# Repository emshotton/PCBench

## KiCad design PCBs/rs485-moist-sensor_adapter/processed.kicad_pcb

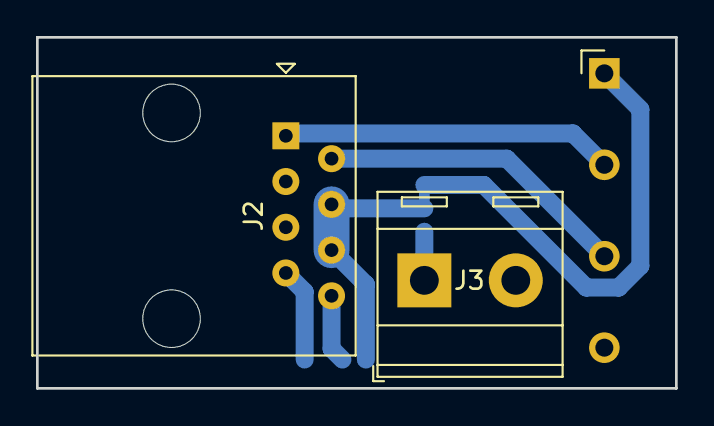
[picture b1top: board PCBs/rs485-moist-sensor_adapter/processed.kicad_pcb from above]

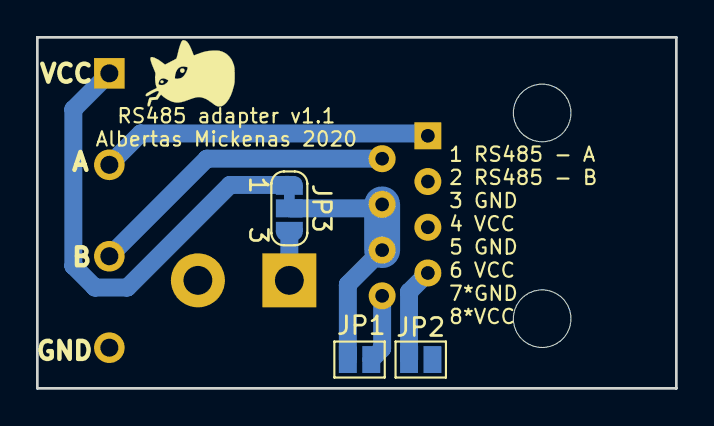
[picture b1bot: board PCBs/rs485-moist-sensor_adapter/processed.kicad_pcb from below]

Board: 2 copper layers, 35.5 x 19.5 mm, 6 parts (3 on the bottom side), 8 nets.

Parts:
J1: Conn_01x04_Male; Pin_Header_Angled_1x04_Pitch2.54mm
J2: RJ45; RJ45_Amphenol_54602-x08_Horizontal
J3: Conn_01x02_Male; TerminalBlock_RND_205-00287_Pitch5.08mm
JP1, JP2: Jumper_2_Open; SolderJumper-2_P1.3mm_Open_Pad1.0x1.5mm
JP3: Jumper_3_Bridged12; SolderJumper-3_P1.3mm_Bridged12_RoundedPad1.0x1.5mm_NumberL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

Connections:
/A: J1.2, J2.1
/A/GND: J2.7, JP2.1
/B: J1.3, J2.2
/B/VCC: J2.8, JP1.1
GND: J1.4, J2.3, J2.5, J3.2, JP2.2
unnamed: J1.1, JP3.1
unnamed: J3.1, JP3.3
VCC: J2.4, J2.6, JP1.2, JP3.2

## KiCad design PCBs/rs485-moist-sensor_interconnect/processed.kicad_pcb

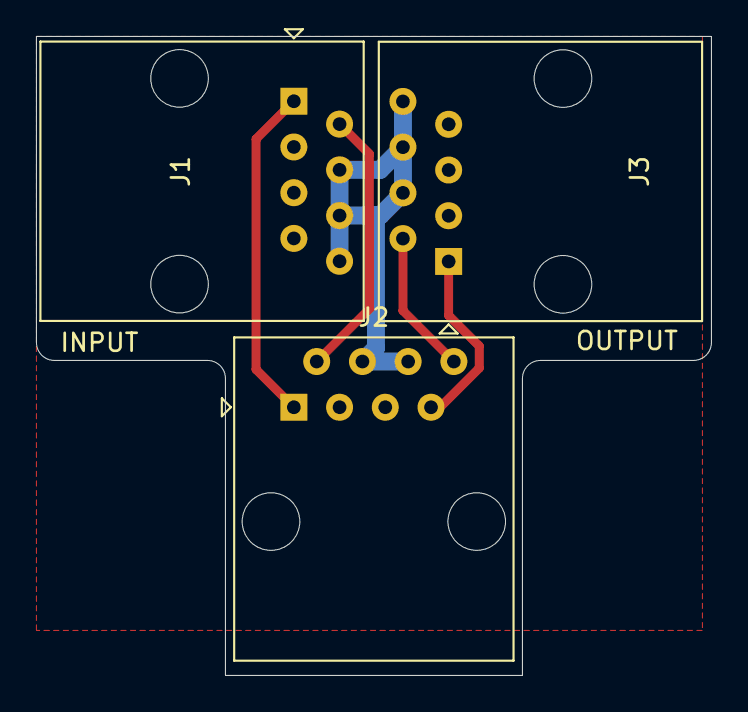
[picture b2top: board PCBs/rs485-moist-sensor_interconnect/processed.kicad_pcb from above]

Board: 2 copper layers, 37.5 x 35.5 mm, 4 parts (1 on the bottom side), 6 nets.

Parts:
C1: C; C_0603_1608Metric_Pad1.05x0.95mm_HandSolder
J1, J2, J3: RJ45; RJ45_Amphenol_54602-x08_Horizontal

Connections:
GND: C1.2, J1.3, J1.5, J1.7, J2.3, J2.5, J3.3, J3.5, J3.7
unnamed: J1.1, J2.1
unnamed: J1.2, J2.2
unnamed: J2.7, J3.1
unnamed: J2.8, J3.2
VCC: C1.1, J1.4, J1.6, J1.8, J2.4, J2.6, J3.4, J3.6, J3.8

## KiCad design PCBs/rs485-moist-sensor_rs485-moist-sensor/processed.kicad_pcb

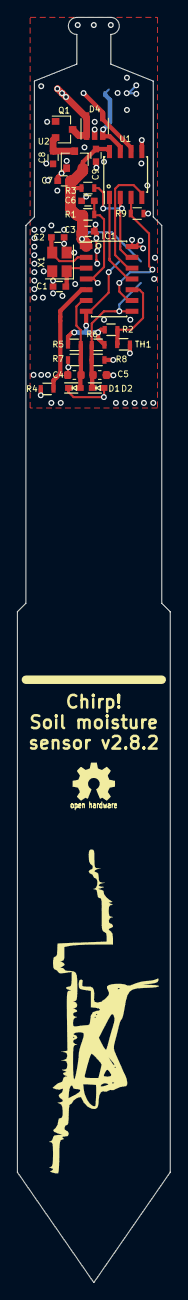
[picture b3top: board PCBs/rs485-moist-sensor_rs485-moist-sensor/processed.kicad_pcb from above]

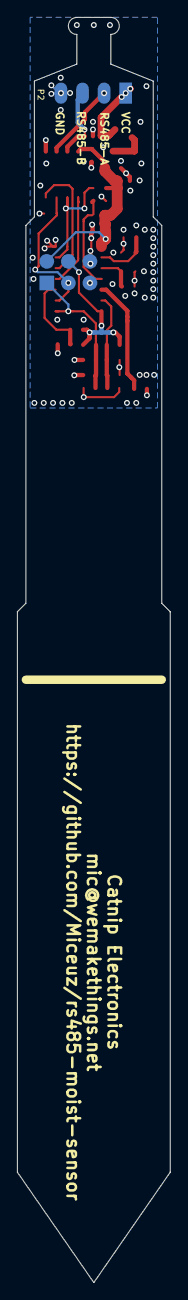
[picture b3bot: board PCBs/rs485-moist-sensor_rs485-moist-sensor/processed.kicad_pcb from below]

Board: 4 copper layers, 18.0 x 149.0 mm, 29 parts (2 on the bottom side), 19 nets.

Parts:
C1, C2: 13p; C_0603
C3, C6, C7, C8, C9: 1u; C_0603
C4, C5: 1n; C_0603_1608Metric
D1, D2: RB751S40; SOD-523
D4: NUP4004M5T1G; SOT-23-5
IC1: ATTINY441-SSU; SOIC-14_3.9x8.7mm_Pitch1.27mm
P1: CONN_02X03; Pin_Header_Straight_2x03
P2: CONN_01X04; Pin_Header_Straight_1x04_Pitch2.54mm
Q1: Q_PMOS_GSD; SOT-23
R1, R3, R9: 10k; R_0603
R2: 10k 0.1%; R_0603
R4: 330; R_0603
R5, R6, R7, R8: 1M; R_0603
TH1: NCP18XH103F03RB; R_0603
U1: SN65HVD72; SOIC-8_3.9x4.9mm_Pitch1.27mm
U2: MCP1702; SOT-23
X1: 16MHz; Crystal_SMD_3225-4pin_3.2x2.5mm

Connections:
+3V3: C3.1, C7.1, C9.1, IC1.1, P1.2, R1.2, R3.1, U1.8, U2.2
/EXCITATION: IC1.5, R4.2
/MOSI: IC1.7, P1.4, R2.1, R5.2, R6.2
/RESET: C6.1, IC1.4, P1.5, R1.1
/RS485A: D4.4, P2.2, U1.6
/RS485B: D4.3, P2.3, U1.7
/RS485_READER_ENABLE: IC1.13, R3.2, U1.2
/RX: IC1.11, U1.1
/SCK: IC1.9, P1.3, R9.1, U1.3
/SENSE_HIGH/MISO: C5.1, D2.2, IC1.8, P1.1, R6.1, R8.2
/SENSE_LOW: C4.1, D1.1, IC1.6, R5.1, R7.2
/SENSOR_TRACK: D1.2, D2.1, R4.1
/THERMISTOR: IC1.10, R2.2, TH1.1
/TX: IC1.12, U1.4
GND: C1.2, C2.2, C3.2, C4.2, C5.2, C6.2, C7.2, C8.2, C9.2, D4.2, IC1.14, P1.6, P2.4, Q1.1, R7.1, R8.1, R9.2, TH1.2, U1.5, U2.1, X1.2, X1.4
unnamed: C1.1, IC1.3, X1.1
unnamed: C2.1, IC1.2, X1.3
unnamed: C8.1, Q1.2, U2.3
VCC: D4.1, D4.5, P2.1, Q1.3

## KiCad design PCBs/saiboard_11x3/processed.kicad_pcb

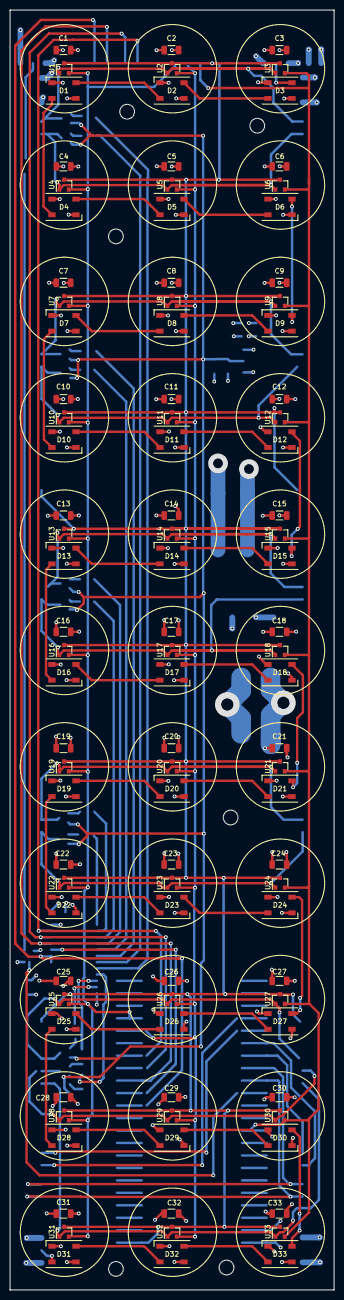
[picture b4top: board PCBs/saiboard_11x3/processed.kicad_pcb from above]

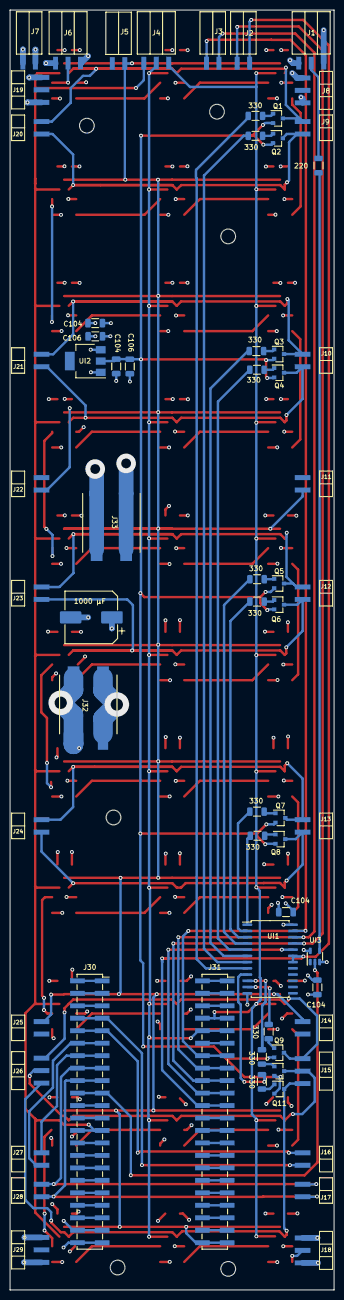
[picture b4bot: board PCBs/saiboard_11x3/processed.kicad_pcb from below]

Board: 4 copper layers, 66.0 x 260.7 mm, 171 parts (66 on the bottom side), 114 nets.

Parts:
C1, C2, C3, C4, C5, C6, C7, C8, C9, C10, C11, C12, C13, C14, C15, C16, C17, C18, C19, C20, C21, C22, C23, C24, C25, C26, C27, C28, C29, C30, C31, C32, C33: C104; C_1206_3216Metric
CI1, CI3, CI4, CI6: C104; C_1206_3216Metric
CI2, CI5: C106; C_1206_3216Metric
CP1: 1000 µF; CP_Elec_10x10.5
D1, D2, D3, D4, D5, D6, D7, D8, D9, D10, D11, D12, D13, D14, D15, D16, D17, D18, D19, D20, D21, D22, D23, D24, D25, D26, D27, D28, D29, D30, D31, D32, D33: SK6812; LED_SK6812_PLCC4_5.0x5.0mm_P3.2mm
J1: Power_top_side_a; PinSocket_1x03_P2.54mm_Horizontal_SMD
J2: IC_top_1; PinSocket_1x02_P2.54mm_Horizontal_SMD
J3: IC_top_2; PinSocket_1x02_P2.54mm_Horizontal_SMD
J4: Hall_top; PinSocket_1x03_P2.54mm_Horizontal_SMD
J5: Touch_top; PinSocket_1x02_P2.54mm_Horizontal_SMD
J6: Power_top; PinSocket_1x03_P2.54mm_Horizontal_SMD
J7: Power_top_side_b; PinSocket_1x02_P2.54mm_Horizontal_SMD
J8: Power_side_a; PinHeader_1x03_P2.54mm_Horizontal_SMD
J9, J10, J12, J13: PQ_side_a; PinHeader_1x02_P2.54mm_Horizontal_SMD
J11: Touch_side_a; PinHeader_1x02_P2.54mm_Horizontal_SMD
J14: Touch_bottom_side_a; PinHeader_1x02_P2.54mm_Horizontal_SMD
J15: PQ_bottom_side_a; PinHeader_1x03_P2.54mm_Horizontal_SMD
J16: Hall_bottom_side_a; PinHeader_1x02_P2.54mm_Horizontal_SMD
J17: IC_bottom_side_a; PinHeader_1x02_P2.54mm_Horizontal_SMD
J18: Power_bottom_side_a; PinHeader_1x03_P2.54mm_Horizontal_SMD
J19: Power_side_b; PinHeader_1x03_P2.54mm_Horizontal_SMD
J20, J21, J23, J24: PQ_side_b; PinHeader_1x02_P2.54mm_Horizontal_SMD
J22: Touch_side_b; PinHeader_1x02_P2.54mm_Horizontal_SMD
J25: Touch_bottom_side_b; PinHeader_1x02_P2.54mm_Horizontal_SMD
J26: PQ_bottom_side_b; PinHeader_1x03_P2.54mm_Horizontal_SMD
J27: Hall_bottom_side_b; PinHeader_1x02_P2.54mm_Horizontal_SMD
J28: IC_bottom_side_b; PinHeader_1x02_P2.54mm_Horizontal_SMD
J29: Power_bottom_side_b; PinHeader_1x03_P2.54mm_Horizontal_SMD
J30: esp32s3left; PinSocket_2x22_P2.54mm_Vertical_SMD
J31: esp32s3right; PinSocket_2x22_P2.54mm_Vertical_SMD
J32: Power_Terminal; Wago_2601-602
J33: Power_RaspberryPi; Wago_2601-602
M1, M2, M5, M6, M6#2, M6#3: MountingHole_3mm
Q1, Q2, Q3, Q4, Q5, Q6, Q7, Q8, Q9, Q10, Q11: 2N3906; SOT-23
R1, R2, R3, R4, R5, R6, R7, R8, R9, R10, R11: 330; R_1206_3216Metric
RI1: 220; R_1206_3216Metric
U1, U2, U3, U4, U5, U6, U7, U8, U9, U10, U11, U12, U13, U14, U15, U16, U17, U18, U19, U20, U21, U22, U23, U24, U25, U26, U27, U28, U29, U30, U31, U32, U33: AH49E; SOT-23
UI1: 74HCT154D; SOP-24_7.5x15.4mm_P1.27mm
UI2: AMS1117-3.3; SOT-223
UI3: SN74LV1T34; SOT-23-5

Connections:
A0: J3.2, J31.13, J31.14, UI1.23 (A0)
A1: J3.1, J31.15, J31.16, UI1.22 (A1)
A2: J2.2, J31.17, J31.18, UI1.21 (A2)
A3: J31.19, J31.20, UI1.20 (A3)
AGND: J5.1, J11.1, J14.2, J22.2, J25.1, J31.43, J31.44, U1.3 (GND), U2.3 (GND), U3.3 (GND), U4.3 (GND), U5.3 (GND), U6.3 (GND), U7.3 (GND), U8.3 (GND), U9.3 (GND), U10.3 (GND), U11.3 (GND), U12.3 (GND), U13.3 (GND), U14.3 (GND), U15.3 (GND), U16.3 (GND), U17.3 (GND), U18.3 (GND), U19.3 (GND), U20.3 (GND), U21.3 (GND), U22.3 (GND), U23.3 (GND), U24.3 (GND), U25.3 (GND), U26.3 (GND), U27.3 (GND), U28.3 (GND), U29.3 (GND), U30.3 (GND), U31.3 (GND), U32.3 (GND), U33.3 (GND)
Additional1: J30.1, J30.2
Additional2: J30.3, J30.4
Additional3: J30.5, J30.6
Additional4: J30.21, J30.22
Additional5: J30.23, J30.24
Additional6: J30.27, J30.28
Additional7: J30.29, J30.30
Additional8: J30.31, J30.32
Additional9: J30.33, J30.34
Additional10: J30.35, J30.36
Additional11: J30.37, J30.38
Additional12: J30.39, J30.40
Additional13: J31.1, J31.2
Additional14: J31.3, J31.4
Additional15: J31.5, J31.6
Additional16: J31.11, J31.12
Additional17: J31.23, J31.24
Additional18: J31.25, J31.26
Additional19: J31.27, J31.28
Additional20: J31.29, J31.30
Additional21: J31.31, J31.32
Additional22: J31.33, J31.34
Additional23: J31.35, J31.36
Additional24: J31.37, J31.38
Additional25: J31.39, J31.40
Additional26: J31.41, J31.42
E: J2.1, J31.21, J31.22, UI1.18 (E0), UI1.19 (E1)
First_LedIn_3V: J30.19, J30.20, UI3.2 (A)
GND: C1.2, C2.2, C3.2, C4.2, C5.2, C6.2, C7.2, C8.2, C9.2, C10.2, C11.2, C12.2, C13.2, C14.2, C15.2, C16.2, C17.2, C18.2, C19.2, C20.2, C21.2, C22.2, C23.2, C24.2, C25.2, C26.2, C27.2, C28.2, C29.2, C30.2, C31.2, C32.2, C33.2, CI1.1, CI2.1, CI3.1, CI4.1, CI5.1, CI6.2, CP1.2, D1.1 (VSS), D2.1 (VSS), D3.1 (VSS), D4.1 (VSS), D5.1 (VSS), D6.1 (VSS), D7.1 (VSS), D8.1 (VSS), D9.1 (VSS), D10.1 (VSS), D11.1 (VSS), D12.1 (VSS), D13.1 (VSS), D14.1 (VSS), D15.1 (VSS), D16.1 (VSS), D17.1 (VSS), D18.1 (VSS), D19.1 (VSS), D20.1 (VSS), D21.1 (VSS), D22.1 (VSS), D23.1 (VSS), D24.1 (VSS), D25.1 (VSS), D26.1 (VSS), D27.1 (VSS), D28.1 (VSS), D29.1 (VSS), D30.1 (VSS), D31.1 (VSS), D32.1 (VSS), D33.1 (VSS), J1.1, J6.3, J7.2, J8.3, J18.3, J19.1, J29.1, J30.43, J30.44, J32.2, J33.2, UI1.12 (GND), UI2.1 (GND), UI3.3 (GND)
HallOut1: J4.1, J31.7, J31.8, U1.2 (OUT), U4.2 (OUT), U7.2 (OUT), U10.2 (OUT), U13.2 (OUT), U16.2 (OUT), U19.2 (OUT), U22.2 (OUT), U25.2 (OUT), U28.2 (OUT), U31.2 (OUT)
HallOut2: J4.2, J31.9, J31.10, U2.2 (OUT), U5.2 (OUT), U8.2 (OUT), U11.2 (OUT), U14.2 (OUT), U17.2 (OUT), U20.2 (OUT), U23.2 (OUT), U26.2 (OUT), U29.2 (OUT), U32.2 (OUT)
HallOut3: J4.3, J30.25, J30.26, U3.2 (OUT), U6.2 (OUT), U9.2 (OUT), U12.2 (OUT), U15.2 (OUT), U18.2 (OUT), U21.2 (OUT), U24.2 (OUT), U27.2 (OUT), U30.2 (OUT), U33.2 (OUT)
HallOut4: J16.1, J30.7, J30.8
HallOut5: J16.2, J30.9, J30.10
HallOut6: J27.2, J30.11, J30.12
HallOut7: J27.1, J30.13, J30.14
LedIn: D31.2 (DIN), J18.2
LedIn_top_side_a: J1.2, RI1.2
LedOut: D3.4 (DOUT), J6.2
unnamed: D1.2 (DIN), D4.4 (DOUT)
unnamed: D1.4 (DOUT), D2.2 (DIN)
unnamed: D2.4 (DOUT), D3.2 (DIN)
unnamed: D4.2 (DIN), D5.4 (DOUT)
unnamed: D5.2 (DIN), D6.4 (DOUT)
unnamed: D6.2 (DIN), D9.4 (DOUT)
unnamed: D7.4 (DOUT), D8.2 (DIN)
unnamed: D8.4 (DOUT), D9.2 (DIN)
unnamed: D10.2 (DIN), D11.4 (DOUT)
unnamed: D7.2 (DIN), D10.4 (DOUT)
unnamed: D11.2 (DIN), D12.4 (DOUT)
unnamed: D12.2 (DIN), D15.4 (DOUT)
unnamed: D13.2 (DIN), D16.4 (DOUT)
unnamed: D13.4 (DOUT), D14.2 (DIN)
unnamed: D14.4 (DOUT), D15.2 (DIN)
unnamed: D16.2 (DIN), D17.4 (DOUT)
unnamed: D17.2 (DIN), D18.4 (DOUT)
unnamed: D18.2 (DIN), D21.4 (DOUT)
unnamed: D19.2 (DIN), D22.4 (DOUT)
unnamed: D19.4 (DOUT), D20.2 (DIN)
unnamed: D20.4 (DOUT), D21.2 (DIN)
unnamed: D22.2 (DIN), D23.4 (DOUT)
unnamed: D23.2 (DIN), D24.4 (DOUT)
unnamed: D24.2 (DIN), D27.4 (DOUT)
unnamed: D25.2 (DIN), D28.4 (DOUT)
unnamed: D25.4 (DOUT), D26.2 (DIN)
unnamed: D26.4 (DOUT), D27.2 (DIN)
unnamed: D28.2 (DIN), D29.4 (DOUT)
unnamed: D29.2 (DIN), D30.4 (DOUT)
unnamed: D30.2 (DIN), D33.4 (DOUT)
unnamed: D31.4 (DOUT), D32.2 (DIN)
unnamed: D32.4 (DOUT), D33.2 (DIN)
unnamed: Q1.1 (B), R1.2
unnamed: Q2.1 (B), R2.2
unnamed: Q3.1 (B), R3.2
unnamed: Q4.1 (B), R4.2
unnamed: Q5.1 (B), R5.2
unnamed: Q6.1 (B), R6.2
unnamed: Q7.1 (B), R7.2
unnamed: Q8.1 (B), R8.2
unnamed: Q9.1 (B), R9.2
unnamed: Q10.1 (B), R10.2
unnamed: Q11.1 (B), R11.2
unnamed: RI1.1, UI3.4 (Y)
P: C1.1, C2.1, C3.1, C4.1, C5.1, C6.1, C7.1, C8.1, C9.1, C10.1, C11.1, C12.1, C13.1, C14.1, C15.1, C16.1, C17.1, C18.1, C19.1, C20.1, C21.1, C22.1, C23.1, C24.1, C25.1, C26.1, C27.1, C28.1, C29.1, C30.1, C31.1, C32.1, C33.1, CI1.2, CI2.2, CI3.2, CI6.1, CP1.1, D1.3 (VDD), D2.3 (VDD), D3.3 (VDD), D4.3 (VDD), D5.3 (VDD), D6.3 (VDD), D7.3 (VDD), D8.3 (VDD), D9.3 (VDD), D10.3 (VDD), D11.3 (VDD), D12.3 (VDD), D13.3 (VDD), D14.3 (VDD), D15.3 (VDD), D16.3 (VDD), D17.3 (VDD), D18.3 (VDD), D19.3 (VDD), D20.3 (VDD), D21.3 (VDD), D22.3 (VDD), D23.3 (VDD), D24.3 (VDD), D25.3 (VDD), D26.3 (VDD), D27.3 (VDD), D28.3 (VDD), D29.3 (VDD), D30.3 (VDD), D31.3 (VDD), D32.3 (VDD), D33.3 (VDD), J1.3, J6.1, J7.1, J8.1, J18.1, J19.3, J29.3, J30.41, J30.42, J32.1, J33.1, UI1.24 (VCC), UI2.3 (VI), UI3.5 (VCC)
P3.3: CI4.2, CI5.2, Q1.2 (E), Q2.2 (E), Q3.2 (E), Q4.2 (E), Q5.2 (E), Q6.2 (E), Q7.2 (E), Q8.2 (E), Q9.2 (E), Q10.2 (E), Q11.2 (E), UI2.2 (VO)
PQ1: J9.2, J20.1, Q1.3 (C), U1.1 (VCC), U2.1 (VCC), U3.1 (VCC)
PQ2: J9.1, J20.2, Q2.3 (C), U4.1 (VCC), U5.1 (VCC), U6.1 (VCC)
PQ3: J10.2, J21.1, Q3.3 (C), U7.1 (VCC), U8.1 (VCC), U9.1 (VCC)
PQ4: J10.1, J21.2, Q4.3 (C), U10.1 (VCC), U11.1 (VCC), U12.1 (VCC)
PQ5: J12.2, J23.1, Q5.3 (C), U13.1 (VCC), U14.1 (VCC), U15.1 (VCC)
PQ6: J12.1, J23.2, Q6.3 (C), U16.1 (VCC), U17.1 (VCC), U18.1 (VCC)
PQ7: J13.2, J24.1, Q7.3 (C), U19.1 (VCC), U20.1 (VCC), U21.1 (VCC)
PQ8: J13.1, J24.2, Q8.3 (C), U22.1 (VCC), U23.1 (VCC), U24.1 (VCC)
PQ9: J15.3, J26.1, Q9.3 (C), U25.1 (VCC), U26.1 (VCC), U27.1 (VCC)
PQ10: J15.2, J26.2, Q10.3 (C), U28.1 (VCC), U29.1 (VCC), U30.1 (VCC)
PQ11: J15.1, J26.3, Q11.3 (C), U31.1 (VCC), U32.1 (VCC), U33.1 (VCC)
Q1: R1.1, UI1.8 (Y7)
Q2: R2.1, UI1.7 (Y6)
Q3: R3.1, UI1.6 (Y5)
Q4: R4.1, UI1.5 (Y4)
Q5: R5.1, UI1.4 (Y3)
Q6: R6.1, UI1.3 (Y2)
Q7: R7.1, UI1.2 (Y1)
Q8: R8.1, UI1.1 (Y0)
Q9: R9.1, UI1.11 (Y10)
Q10: R10.1, UI1.10 (Y9)
Q11: R11.1, UI1.9 (Y8)
S0: J17.2, J28.1, J30.15, J30.16
S1: J17.1, J28.2, J30.17, J30.18

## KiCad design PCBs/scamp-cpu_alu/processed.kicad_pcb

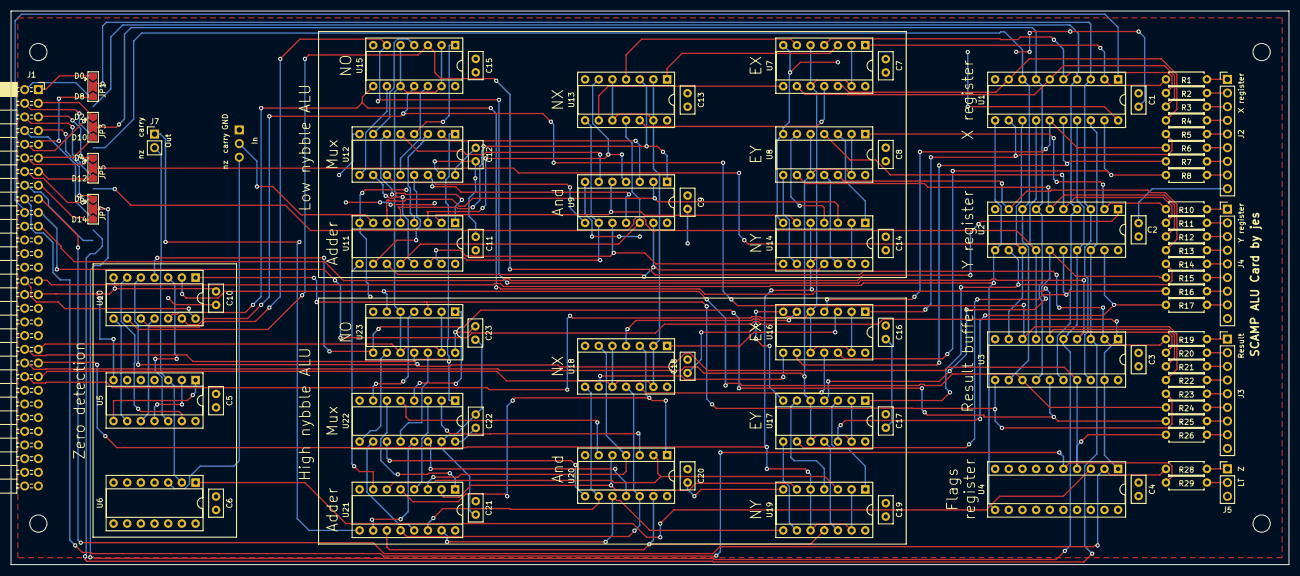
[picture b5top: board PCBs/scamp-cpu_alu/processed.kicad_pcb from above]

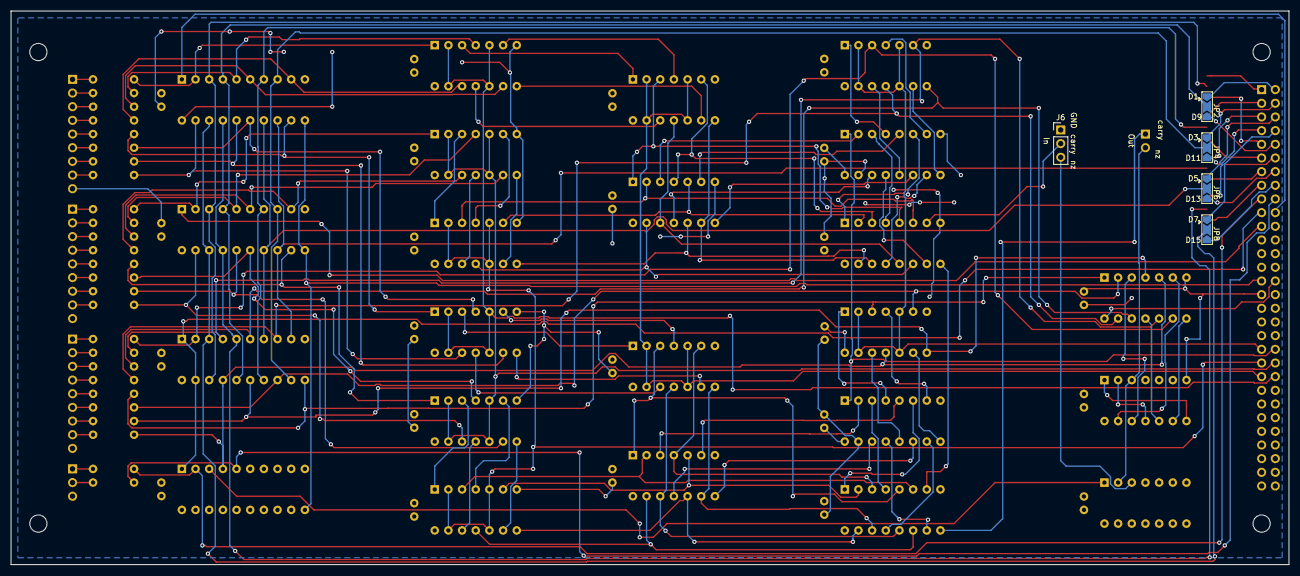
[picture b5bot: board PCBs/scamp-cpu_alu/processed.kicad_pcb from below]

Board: 2 copper layers, 237.5 x 102.9 mm, 87 parts (5 on the bottom side), 156 nets.

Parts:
C1, C2, C3, C4, C5, C6, C7, C8, C9, C10, C11, C12, C13, C14, C15, C16, C17, C18, C19, C20, C21, C22, C23: C; C_Disc_D5.0mm_W2.5mm_P2.50mm
J1: Conn_02x30_Counter_Clockwise; PinSocket_2x30_P2.54mm_Horizontal
J2, J3, J4: Conn_01x09_Male; PinHeader_1x09_P2.54mm_Vertical
J5, J6: Conn_01x03_Male; PinHeader_1x03_P2.54mm_Vertical
J7: Conn_01x02_Male; PinHeader_1x02_P2.54mm_Vertical
JP1, JP2, JP3, JP4, JP5, JP6, JP7, JP8: SolderJumper_3_Bridged12; SolderJumper-3_P2.0mm_Open_TrianglePad1.0x1.5mm
R1, R2, R3, R4, R5, R6, R7, R8, R10, R11, R12, R13, R14, R15, R16, R17, R19, R20, R21, R22, R23, R24, R25, R26, R28, R29: R; R_Axial_DIN0207_L6.3mm_D2.5mm_P7.62mm_Horizontal
U1, U2, U4: 74LS377; DIP-20_W7.62mm_Socket
U3: 74LS244; DIP-20_W7.62mm_Socket
U5, U10: 74LS32; DIP-14_W7.62mm_Socket
U6: 74LS02; DIP-14_W7.62mm_Socket
U7, U8, U9, U16, U17, U20: 74LS08; DIP-14_W7.62mm_Socket
U11, U21: 74LS283; DIP-16_W7.62mm_Socket
U12, U22: 74LS157; DIP-16_W7.62mm_Socket
U13, U14, U15, U18, U19, U23: 74LS86; DIP-14_W7.62mm_Socket

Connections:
/aluhigh/C_in: U11.9, U21.7
CLK: J1.29, U1.11, U2.11, U4.11
D0: J1.1, JP1.1
D0h: JP1.2, U1.3, U2.3, U3.18
D1: J1.2, JP2.1
D1h: JP2.2, U1.4, U2.4, U3.16
D2: J1.3, JP3.1
D2h: JP3.2, U1.7, U2.7, U3.14
D3: J1.4, JP4.1
D3h: JP4.2, U1.8, U2.8, U3.12
D4: J1.5, JP5.1
D4h: JP5.2, U1.13, U2.13, U3.9
D5: J1.6, JP6.1
D5h: JP6.2, U1.14, U2.14, U3.7
D6: J1.7, JP7.1
D6h: JP7.2, U1.17, U2.17, U3.5
D7: J1.8, JP8.1
D7h: JP8.2, U1.18, U2.18, U3.3
D8: J1.9, JP1.3
D9: J1.10, JP2.3
D10: J1.11, JP3.3
D11: J1.12, JP4.3
D12: J1.13, JP5.3
D13: J1.14, JP6.3
D14: J1.15, JP7.3
D15: J1.16, JP8.3
E0: R19.1, U3.2, U10.9, U15.3
E1: R20.1, U3.4, U10.10, U15.6
E2: R21.1, U3.6, U10.12, U15.8
E3: R22.1, U3.8, U10.13, U15.11
E4: R23.1, U3.11, U10.1, U23.3
E5: R24.1, U3.13, U10.2, U23.6
E6: R25.1, U3.15, U10.4, U23.8
E7: R26.1, U3.17, U4.4, U10.5, U23.11
EX: J1.44, U7.2, U7.5, U7.10, U7.13, U16.2, U16.5, U16.10, U16.13
EY: J1.42, U8.2, U8.5, U8.10, U8.13, U17.2, U17.5, U17.10, U17.13
F: J1.40, U12.1, U22.1
GND: C1.2, C2.2, C3.2, C4.2, C5.2, C6.2, C7.2, C8.2, C9.2, C10.2, C11.2, C12.2, C13.2, C14.2, C15.2, C16.2, C17.2, C18.2, C19.2, C20.1, C21.1, C22.1, C23.1, J1.31, J2.9, J3.9, J4.9, J5.3, J6.1, U1.10, U2.10, U3.10, U4.10, U5.7, U6.7, U7.7, U8.7, U9.7, U10.7, U11.8, U12.8, U12.15, U13.7, U14.7, U15.7, U16.7, U17.7, U18.7, U19.7, U20.7, U21.8, U22.8, U22.15, U23.7
LT: J1.18, R29.1, U4.5
NO: J1.39, U15.2, U15.5, U15.10, U15.13, U23.2, U23.5, U23.10, U23.13
NX: J1.43, U13.2, U13.5, U13.10, U13.13, U18.2, U18.5, U18.10, U18.13
NY: J1.41, U14.2, U14.5, U14.10, U14.13, U19.2, U19.5, U19.10, U19.13
unnamed: J2.1, R1.2
unnamed: J2.2, R2.2
unnamed: J2.3, R3.2
unnamed: J2.4, R4.2
unnamed: J2.5, R5.2
unnamed: J2.6, R6.2
unnamed: J2.7, R7.2
unnamed: J2.8, R8.2
unnamed: J3.1, R19.2
unnamed: J3.2, R20.2
unnamed: J3.3, R21.2
unnamed: J3.4, R22.2
unnamed: J3.5, R23.2
unnamed: J3.6, R24.2
unnamed: J3.7, R25.2
unnamed: J3.8, R26.2
unnamed: J4.1, R10.2
unnamed: J4.2, R11.2
unnamed: J4.3, R12.2
unnamed: J4.4, R13.2
unnamed: J4.5, R14.2
unnamed: J4.6, R15.2
unnamed: J4.7, R16.2
unnamed: J4.8, R17.2
unnamed: J5.1, R28.2
unnamed: J5.2, R29.2
unnamed: U5.1, U5.8
unnamed: U5.2, U5.11
unnamed: U5.12, U10.3
unnamed: U5.13, U10.6
unnamed: U5.9, U10.8
unnamed: U5.10, U10.11
unnamed: U11.1, U12.6
unnamed: U9.5, U11.2, U14.6
unnamed: U9.4, U11.3, U13.6
unnamed: U11.4, U12.3
unnamed: U9.1, U11.5, U13.3
unnamed: U9.2, U11.6, U14.3
unnamed: U11.10, U12.13
unnamed: U9.13, U11.11, U14.11
unnamed: U9.12, U11.12, U13.11
unnamed: U11.13, U12.10
unnamed: U9.9, U11.14, U13.8
unnamed: U9.10, U11.15, U14.8
unnamed: U9.3, U12.2
unnamed: U12.4, U15.1
unnamed: U9.6, U12.5
unnamed: U12.7, U15.4
unnamed: U12.9, U15.9
unnamed: U9.8, U12.11
unnamed: U12.12, U15.12
unnamed: U9.11, U12.14
unnamed: U7.3, U13.1
unnamed: U7.6, U13.4
unnamed: U7.8, U13.9
unnamed: U7.11, U13.12
unnamed: U8.3, U14.1
unnamed: U8.6, U14.4
unnamed: U8.8, U14.9
unnamed: U8.11, U14.12
unnamed: U16.3, U18.1
unnamed: U16.6, U18.4
unnamed: U16.8, U18.9
unnamed: U16.11, U18.12
unnamed: U17.3, U19.1
unnamed: U17.6, U19.4
unnamed: U17.8, U19.9
unnamed: U17.11, U19.12
unnamed: U18.3, U20.1, U21.5
unnamed: U18.6, U20.4, U21.3
unnamed: U18.8, U20.9, U21.14
unnamed: U18.11, U20.12, U21.12
unnamed: U19.3, U20.2, U21.6
unnamed: U19.6, U20.5, U21.2
unnamed: U19.8, U20.10, U21.15
unnamed: U19.11, U20.13, U21.11
unnamed: U20.3, U22.2
unnamed: U20.6, U22.5
unnamed: U20.8, U22.11
unnamed: U20.11, U22.14
unnamed: U21.1, U22.6
unnamed: U21.4, U22.3
unnamed: U21.10, U22.13
unnamed: U21.13, U22.10
unnamed: U22.4, U23.1
unnamed: U22.7, U23.4
unnamed: U22.9, U23.9
unnamed: U22.12, U23.12
VCC: C1.1, C2.1, C3.1, C4.1, C5.1, C6.1, C7.1, C8.1, C9.1, C10.1, C11.1, C12.1, C13.1, C14.1, C15.1, C16.1, C17.1, C18.1, C19.1, C20.2, C21.2, C22.2, C23.2, J1.30, U1.20, U2.20, U3.20, U4.20, U5.14, U6.14, U7.14, U8.14, U9.14, U10.14, U11.16, U12.16, U13.14, U14.14, U15.14, U16.14, U17.14, U18.14, U19.14, U20.14, U21.16, U22.16, U23.14
X0: R1.1, U1.2, U7.1
X1: R2.1, U1.5, U7.4
X2: R3.1, U1.6, U7.9
X3: R4.1, U1.9, U7.12
X4: R5.1, U1.12, U16.1
X5: R6.1, U1.15, U16.4
X6: R7.1, U1.16, U16.9
X7: R8.1, U1.19, U16.12
Y0: R10.1, U2.2, U8.1
Y1: R11.1, U2.5, U8.4
Y2: R12.1, U2.6, U8.9
Y3: R13.1, U2.9, U8.12
Y4: R14.1, U2.12, U17.1
Y5: R15.1, U2.15, U17.4
Y6: R16.1, U2.16, U17.9
Y7: R17.1, U2.19, U17.12
Z: J1.17, R28.1, U4.2
Z_new: U4.3, U6.1
carry_in: J6.2, U11.7
carry_out: J7.1, U21.9
nz1: J7.2, U5.3, U6.2
nz2: J6.3, U6.3
~EO~: J1.19, U3.1, U3.19, U4.1
~XI~: J1.20, U1.1
~YI~: J1.21, U2.1

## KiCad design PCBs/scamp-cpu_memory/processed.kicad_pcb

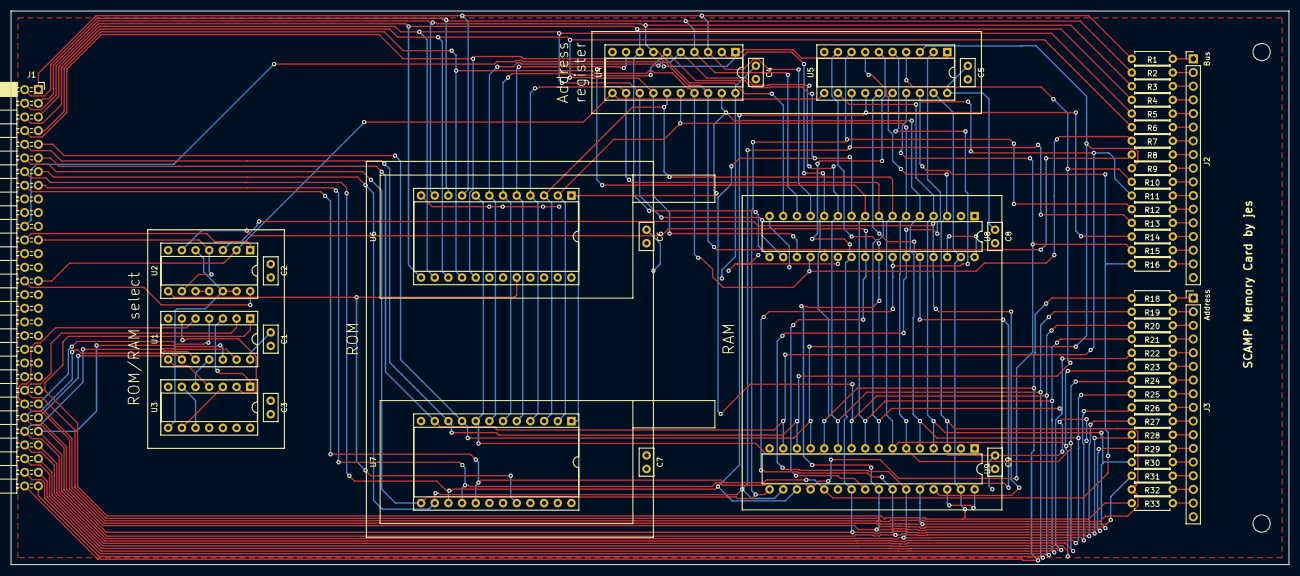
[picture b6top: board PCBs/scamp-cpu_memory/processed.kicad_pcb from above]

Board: 2 copper layers, 237.5 x 102.9 mm, 53 parts (0 on the bottom side), 81 nets.

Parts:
C1, C2, C3, C4, C5, C6, C7, C8, C9: C; C_Disc_D5.0mm_W2.5mm_P2.50mm
J1: Conn_02x30_Counter_Clockwise; PinSocket_2x30_P2.54mm_Horizontal
J2, J3: Conn_01x17_Male; PinHeader_1x17_P2.54mm_Vertical
R1, R2, R3, R4, R5, R6, R7, R8, R9, R10, R11, R12, R13, R14, R15, R16, R18, R19, R20, R21, R22, R23, R24, R25, R26, R27, R28, R29, R30, R31, R32, R33: R; R_Axial_DIN0207_L6.3mm_D2.5mm_P7.62mm_Horizontal
U1, U3: 74LS32; DIP-14_W7.62mm_Socket
U2: 74LS00; DIP-14_W7.62mm_Socket
U4, U5: 74LS377; DIP-20_W7.62mm_Socket
U6, U7: 28C16; DIP-24_W15.24mm_Socket
U8, U9: W24512A; DIP-32_W7.62mm

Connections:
A0: J1.60, R18.1, U4.2, U6.8, U7.8, U8.12, U9.12
A1: J1.59, R19.1, U4.5, U6.7, U7.7, U8.11, U9.11
A2: J1.58, R20.1, U4.6, U6.6, U7.6, U8.10, U9.10
A3: J1.57, R21.1, U4.9, U6.5, U7.5, U8.9, U9.9
A4: J1.56, R22.1, U4.12, U6.4, U7.4, U8.8, U9.8
A5: J1.55, R23.1, U4.15, U6.3, U7.3, U8.7, U9.7
A6: J1.54, R24.1, U4.16, U6.2, U7.2, U8.6, U9.6
A7: J1.53, R25.1, U4.19, U6.1, U7.1, U8.5, U9.5
A8: J1.52, R26.1, U1.13, U5.2, U8.27, U9.27
A9: J1.51, R27.1, U1.12, U5.5, U8.26, U9.26
A10: J1.50, R28.1, U1.10, U5.6, U8.23, U9.23
A11: J1.49, R29.1, U1.9, U5.9, U8.25, U9.25
A12: J1.48, R30.1, U1.5, U5.12, U8.4, U9.4
A13: J1.47, R31.1, U1.4, U5.15, U8.28, U9.28
A14: J1.46, R32.1, U1.2, U5.16, U8.3, U9.3
A15: J1.45, R33.1, U1.1, U5.19, U8.31, U9.31
CLK: J1.29, U2.2, U4.11, U5.11
D0: J1.1, R1.1, U4.3, U6.9, U8.13
D1: J1.2, R2.1, U4.4, U6.10, U8.14
D2: J1.3, R3.1, U4.7, U6.11, U8.15
D3: J1.4, R4.1, U4.8, U6.13, U8.17
D4: J1.5, R5.1, U4.13, U6.14, U8.18
D5: J1.6, R6.1, U4.14, U6.15, U8.19
D6: J1.7, R7.1, U4.17, U6.16, U8.20
D7: J1.8, R8.1, U4.18, U6.17, U8.21
D8: J1.9, R9.1, U5.3, U7.9, U9.13
D9: J1.10, R10.1, U5.4, U7.10, U9.14
D10: J1.11, R11.1, U5.7, U7.11, U9.15
D11: J1.12, R12.1, U5.8, U7.13, U9.17
D12: J1.13, R13.1, U5.13, U7.14, U9.18
D13: J1.14, R14.1, U5.14, U7.15, U9.19
D14: J1.15, R15.1, U5.17, U7.16, U9.20
D15: J1.16, R16.1, U5.18, U7.17, U9.21
GND: C1.2, C2.2, C3.2, C4.2, C5.2, C6.2, C7.2, C8.2, C9.2, J1.31, J2.17, J3.17, U1.7, U2.7, U3.7, U4.10, U5.10, U6.12, U6.18, U6.19, U6.22, U6.23, U7.12, U7.18, U7.19, U7.22, U7.23, U8.16, U8.22, U9.16, U9.22
MI: J1.24, U2.1
MO: J1.23, U2.4, U2.9
unnamed: J2.1, R1.2
unnamed: J2.2, R2.2
unnamed: J2.3, R3.2
unnamed: J2.4, R4.2
unnamed: J2.5, R5.2
unnamed: J2.6, R6.2
unnamed: J2.7, R7.2
unnamed: J2.8, R8.2
unnamed: J2.9, R9.2
unnamed: J2.10, R10.2
unnamed: J2.11, R11.2
unnamed: J2.12, R12.2
unnamed: J2.13, R13.2
unnamed: J2.14, R14.2
unnamed: J2.15, R15.2
unnamed: J2.16, R16.2
unnamed: J3.1, R18.2
unnamed: J3.2, R19.2
unnamed: J3.3, R20.2
unnamed: J3.4, R21.2
unnamed: J3.5, R22.2
unnamed: J3.6, R23.2
unnamed: J3.7, R24.2
unnamed: J3.8, R25.2
unnamed: J3.9, R26.2
unnamed: J3.10, R27.2
unnamed: J3.11, R28.2
unnamed: J3.12, R29.2
unnamed: J3.13, R30.2
unnamed: J3.14, R31.2
unnamed: J3.15, R32.2
unnamed: J3.16, R33.2
unnamed: U1.3, U3.1
unnamed: U1.6, U3.2
unnamed: U1.8, U3.4
unnamed: U1.11, U3.5
unnamed: U2.10, U2.11
unnamed: U3.3, U3.9
unnamed: U3.6, U3.10
VCC: C1.1, C2.1, C3.1, C4.1, C5.1, C6.1, C7.1, C8.1, C9.1, J1.30, U1.14, U2.14, U3.14, U4.20, U5.20, U6.21, U6.24, U7.21, U7.24, U8.30, U8.32, U9.30, U9.32
want_ram: U2.5, U2.12, U2.13, U3.8
~AI~: J1.22, U4.1, U5.1
~LOAD_CLK~: U2.3, U8.29, U9.29
~RAM_EN~: U2.6, U8.24, U9.24
~ROM_EN~: U2.8, U6.20, U7.20

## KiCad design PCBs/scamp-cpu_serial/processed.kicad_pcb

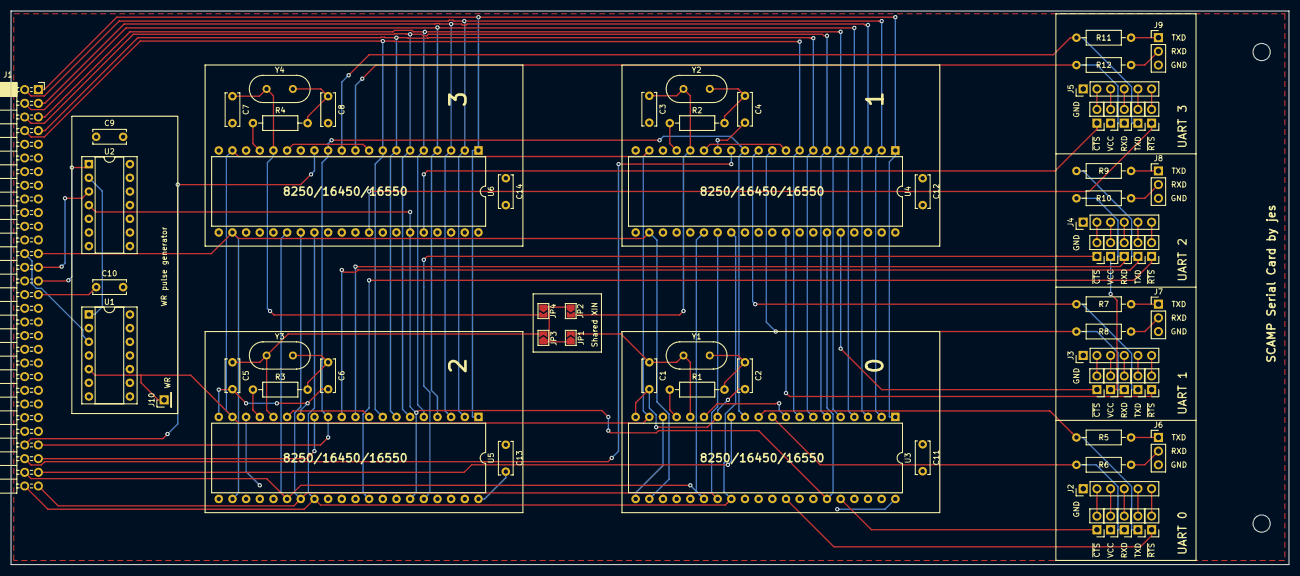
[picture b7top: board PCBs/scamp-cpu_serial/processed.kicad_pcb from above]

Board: 2 copper layers, 237.5 x 102.9 mm, 62 parts (0 on the bottom side), 70 nets.

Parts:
C1, C2, C3, C4, C5, C6, C7, C8, C9, C10, C11, C12, C13, C14: C; C_Disc_D6.0mm_W2.5mm_P5.00mm
J1: Conn_02x30_Counter_Clockwise; PinSocket_2x30_P2.54mm_Horizontal
J2, J3, J4, J5: Conn_01x06_Male; PinHeader_1x06_P2.54mm_Vertical
J6, J7, J8, J9: Conn_01x03_Male; PinHeader_1x03_P2.54mm_Vertical
J10: Conn_01x01_Male; PinHeader_1x01_P2.54mm_Vertical
JP1, JP2, JP3, JP4: SolderJumper_2_Open; SolderJumper-2_P1.3mm_Open_TrianglePad1.0x1.5mm
R1, R2, R3, R4, R5, R6, R7, R8, R9, R10, R11, R12: R; R_Axial_DIN0207_L6.3mm_D2.5mm_P10.16mm_Horizontal
RXD: Jumper_NO_Small; PinHeader_1x02_P2.54mm_Vertical
RXD#2, RXD#3, RXD#4: Jumper_NO_Small; PinHeader_1x02_P2.54mm_Vertical
TXD: Jumper_NO_Small; PinHeader_1x02_P2.54mm_Vertical
TXD#2, TXD#3, TXD#4: Jumper_NO_Small; PinHeader_1x02_P2.54mm_Vertical
U1: 74LS74; DIP-14_W7.62mm_Socket
U2: 74LS04; DIP-14_W7.62mm_Socket
U3, U4, U5, U6: 8250; DIP-40_W15.24mm
VCC: Jumper_NO_Small; PinHeader_1x02_P2.54mm_Vertical
VCC#2, VCC#3, VCC#4: Jumper_NO_Small; PinHeader_1x02_P2.54mm_Vertical
Y1, Y2, Y3, Y4: Crystal; Crystal_HC49-U_Vertical

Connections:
/uart8250a/RXD: R6.2, RXD.1, U3.10
/uart8250a/TXD: R5.2, TXD.1, U3.11
/uart8250b/RXD: R8.2, RXD#2.1, U4.10
/uart8250b/TXD: R7.2, TXD#2.1, U4.11
/uart8250c/RXD: R10.2, RXD#3.1, U5.10
/uart8250c/TXD: R9.2, TXD#3.1, U5.11
/uart8250d/RXD: R12.2, RXD#4.1, U6.10
/uart8250d/TXD: R11.2, TXD#4.1, U6.11
A0: J1.60, U3.28, U4.28, U5.28, U6.28
A1: J1.59, U3.27, U4.27, U5.27, U6.27
A2: J1.58, U3.26, U4.26, U5.26, U6.26
A3: J1.57, U3.13
A4: J1.56, U4.13
A5: J1.55, U5.13
A6: J1.54, U6.13
A7: J1.53, U3.12, U4.12, U5.12, U6.12
CLK: J1.29, U2.1
D0: J1.1, U3.1, U4.1, U5.1, U6.1
D1: J1.2, U3.2, U4.2, U5.2, U6.2
D2: J1.3, U3.3, U4.3, U5.3, U6.3
D3: J1.4, U3.4, U4.4, U5.4, U6.4
D4: J1.5, U3.5, U4.5, U5.5, U6.5
D5: J1.6, U3.6, U4.6, U5.6, U6.6
D6: J1.7, U3.7, U4.7, U5.7, U6.7
D7: J1.8, U3.8, U4.8, U5.8, U6.8
DI: J1.26, U1.3
DO: J1.25, U3.22, U4.22, U5.22, U6.22
GND: C1.2, C2.2, C3.2, C4.2, C5.2, C6.2, C7.2, C8.2, C9.2, C10.2, C11.2, C12.2, C13.2, C14.2, J1.31, J2.1, J3.1, J4.1, J5.1, J6.3, J7.3, J8.3, J9.3, U1.7, U2.7, U3.14, U3.20, U3.25, U4.14, U4.20, U4.25, U5.14, U5.20, U5.25, U6.14, U6.20, U6.25
unnamed: C1.1, JP1.2, U3.16, Y1.1
unnamed: C2.1, R1.2, Y1.2
unnamed: C3.1, JP2.2, U4.16, Y2.1
unnamed: C4.1, R2.2, Y2.2
unnamed: C5.1, JP3.2, U5.16, Y3.1
unnamed: C6.1, R3.2, Y3.2
unnamed: C7.1, JP4.2, U6.16, Y4.1
unnamed: C8.1, R4.2, Y4.2
unnamed: J2.3, VCC.2
unnamed: J2.4, RXD.2
unnamed: J2.5, TXD.2
unnamed: J3.3, VCC#2.2
unnamed: J3.4, RXD#2.2
unnamed: J3.5, TXD#2.2
unnamed: J4.3, VCC#3.2
unnamed: J4.4, RXD#3.2
unnamed: J4.5, TXD#3.2
unnamed: J5.3, VCC#4.2
unnamed: J5.4, RXD#4.2
unnamed: J5.5, TXD#4.2
unnamed: J6.1, R5.1
unnamed: J6.2, R6.1
unnamed: J7.1, R7.1
unnamed: J7.2, R8.1
unnamed: J8.1, R9.1
unnamed: J8.2, R10.1
unnamed: J9.1, R11.1
unnamed: J9.2, R12.1
unnamed: R1.1, U3.17
unnamed: R2.1, U4.17
unnamed: R3.1, U5.17
unnamed: R4.1, U6.17
unnamed: U3.9, U3.15
unnamed: U4.9, U4.15
unnamed: U5.9, U5.15
unnamed: U6.9, U6.15
SHAREDXIN: JP1.1, JP2.1, JP3.1, JP4.1
VCC: C9.1, C10.1, C11.1, C12.1, C13.1, C14.1, J1.30, U1.2, U1.4, U1.14, U2.14, U3.18, U3.21, U3.40, U4.18, U4.21, U4.40, U5.18, U5.21, U5.40, U6.18, U6.21, U6.40, VCC.1, VCC#2.1, VCC#3.1, VCC#4.1
WR: J10.1, U1.5, U3.19, U4.19, U5.19, U6.19
inv_CLK: U1.1, U2.2
inv_~RESET: U2.4, U3.35, U4.35, U5.35, U6.35
~RESET: J1.27, U2.3

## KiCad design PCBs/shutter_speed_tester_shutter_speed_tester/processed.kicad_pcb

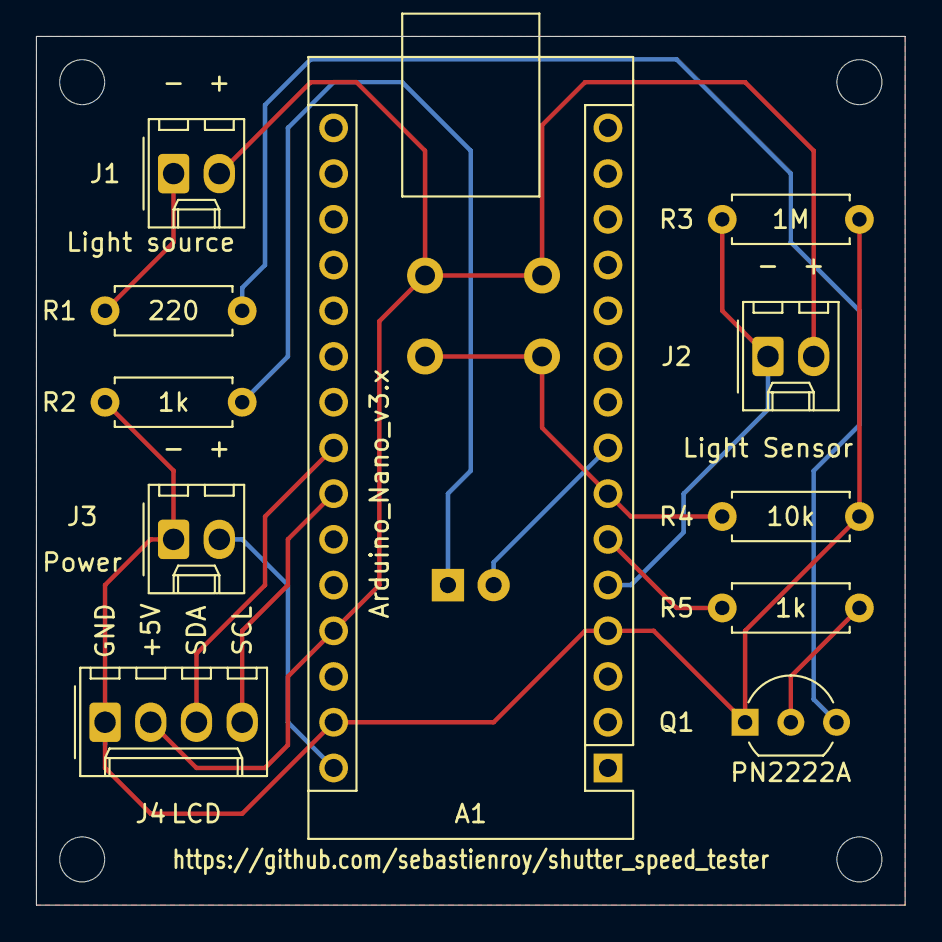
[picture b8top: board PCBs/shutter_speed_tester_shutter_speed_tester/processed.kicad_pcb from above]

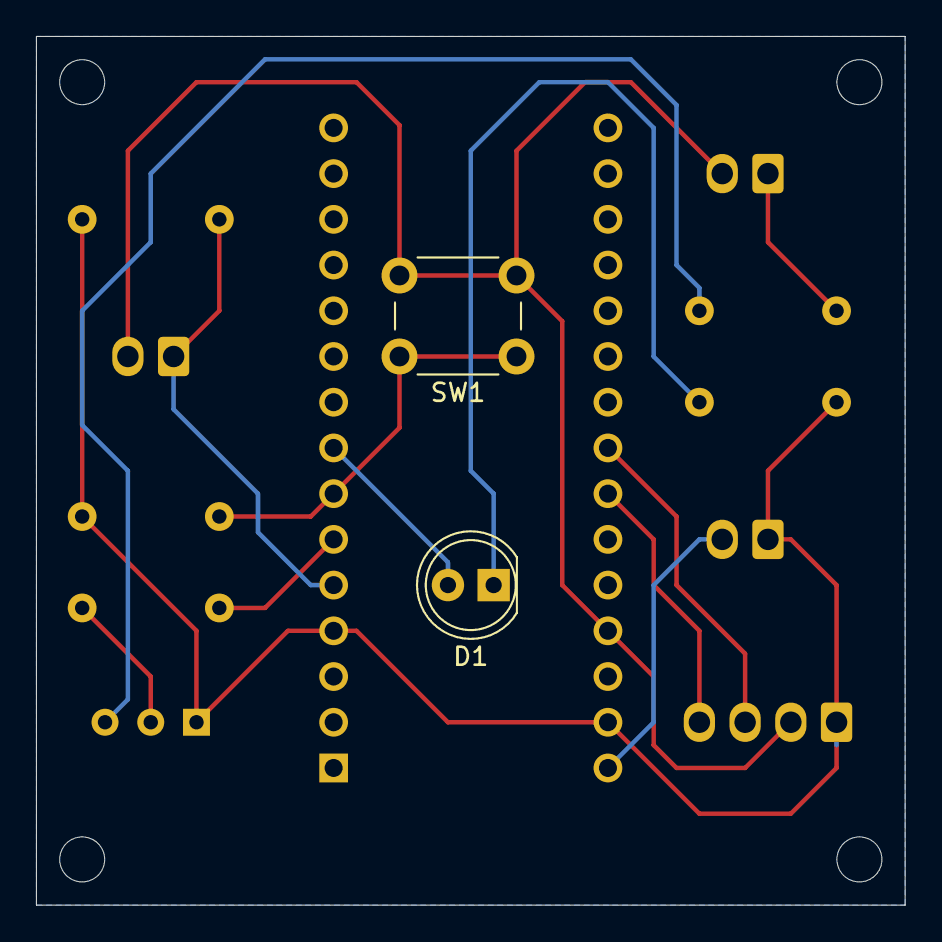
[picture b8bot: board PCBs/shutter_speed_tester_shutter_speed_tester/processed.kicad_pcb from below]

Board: 2 copper layers, 48.3 x 48.3 mm, 17 parts (2 on the bottom side), 13 nets.

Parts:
A1: Arduino_Nano_v3.x; Arduino_Nano
D1: Control LED; LED_D5.0mm
H1, H2, H3, H4: MountingHole; MountingHole_2.5mm
J1: Light source; Molex_KK-254_AE-6410-02A_1x02_P2.54mm_Vertical
J2: Light Sensor; Molex_KK-254_AE-6410-02A_1x02_P2.54mm_Vertical
J3: Power; Molex_KK-254_AE-6410-02A_1x02_P2.54mm_Vertical
J4: LCD; Molex_KK-254_AE-6410-04A_1x04_P2.54mm_Vertical
Q1: PN2222A; TO-92_Inline_Wide
R1: 220; R_Axial_DIN0207_L6.3mm_D2.5mm_P7.62mm_Horizontal
R2, R5: 1k; R_Axial_DIN0207_L6.3mm_D2.5mm_P7.62mm_Horizontal
R3: 1M; R_Axial_DIN0207_L6.3mm_D2.5mm_P7.62mm_Horizontal
R4: 10k; R_Axial_DIN0207_L6.3mm_D2.5mm_P7.62mm_Horizontal
SW1: Reset switch; SW_PUSH_6mm_H5mm

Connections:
GND: A1.4, A1.29, J3.1, J4.1, Q1.1, R2.2, R3.2, R4.2
unnamed: A1.5, J2.1, R3.1
unnamed: A1.6, R5.1
unnamed: A1.7, R4.1, SW1.1
unnamed: A1.8, D1.2
unnamed: A1.23, J4.3
unnamed: A1.24, J4.4
unnamed: A1.27, J1.2, J2.2, J4.2, SW1.2
unnamed: A1.30, J3.2
unnamed: D1.1, R2.1
unnamed: J1.1, R1.1
unnamed: Q1.2, R5.2
unnamed: Q1.3, R1.2
